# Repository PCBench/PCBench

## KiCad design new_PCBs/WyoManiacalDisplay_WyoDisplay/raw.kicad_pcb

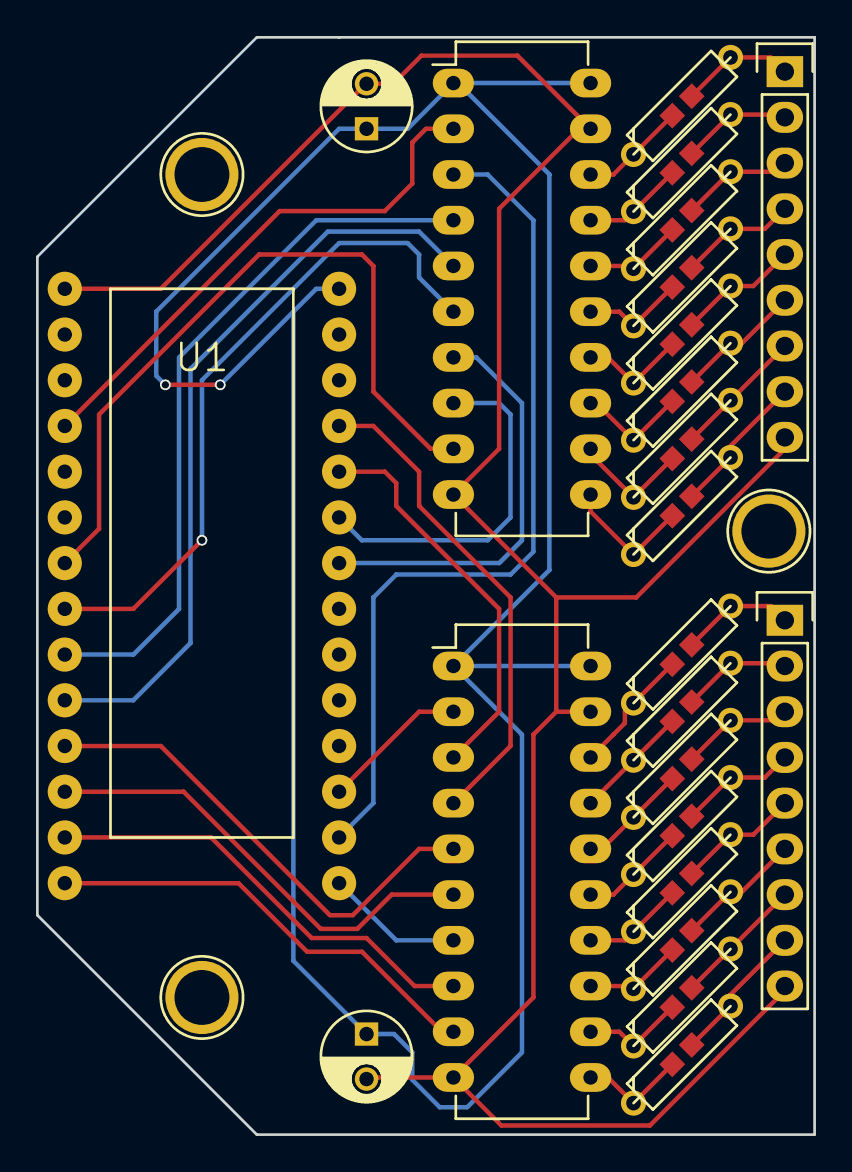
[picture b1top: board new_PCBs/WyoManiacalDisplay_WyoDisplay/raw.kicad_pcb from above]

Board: 2 copper layers, 43.2 x 61.0 mm, 23 parts (0 on the bottom side), 50 nets.

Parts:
C1, C2: 0.1uF; C_Radial_D5_L6_P2.5
P1: OUT1; Socket_Strip_Straight_1x09
P2: OUT2; Socket_Strip_Straight_1x09
R1, R2, R3, R4, R5, R6, R7, R8, R9, R10, R11, R12, R13, R14, R15, R16: R_Small; R-1-8w
U1: Teensy_3.1; Teensy-3.1
U2, U3: 74HCT245; DIP-20_W7.62mm_LongPads

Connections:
2: U1.2, U2.2
5: U1.5, U2.9
6: U1.6, U2.6
7: U1.7, U2.4
8: U1.8, U2.5
9: U1.9, U3.5
10: U1.10, U3.6
11: U1.11, U3.8
12: U1.12, U3.9
13: U1.13, U3.7
14: U1.14, U2.3
15: U1.15, U3.2
20: U1.20, U2.7
21: U1.21, U2.8
22: U1.22, U3.3
23: U1.23, U3.4
GND: C1.2, C2.2, P1.9, P2.9, U1.27, U2.10, U2.19, U3.10, U3.19
unnamed: P1.1, R1.2
unnamed: P1.2, R2.2
unnamed: P1.3, R3.2
unnamed: P1.4, R4.2
unnamed: P1.5, R5.2
unnamed: P1.6, R6.2
unnamed: P1.7, R7.2
unnamed: P1.8, R8.2
unnamed: P2.1, R9.2
unnamed: P2.2, R10.2
unnamed: P2.3, R11.2
unnamed: P2.4, R12.2
unnamed: P2.5, R13.2
unnamed: P2.6, R14.2
unnamed: P2.7, R15.2
unnamed: P2.8, R16.2
unnamed: R1.1, U2.18
unnamed: R2.1, U2.17
unnamed: R3.1, U2.16
unnamed: R4.1, U2.15
unnamed: R5.1, U2.14
unnamed: R6.1, U2.13
unnamed: R7.1, U2.12
unnamed: R8.1, U2.11
unnamed: R9.1, U3.18
unnamed: R10.1, U3.17
unnamed: R11.1, U3.16
unnamed: R12.1, U3.15
unnamed: R13.1, U3.14
unnamed: R14.1, U3.13
unnamed: R15.1, U3.12
unnamed: R16.1, U3.11
VCC: C1.1, C2.1, U1.26, U2.1, U2.20, U3.1, U3.20

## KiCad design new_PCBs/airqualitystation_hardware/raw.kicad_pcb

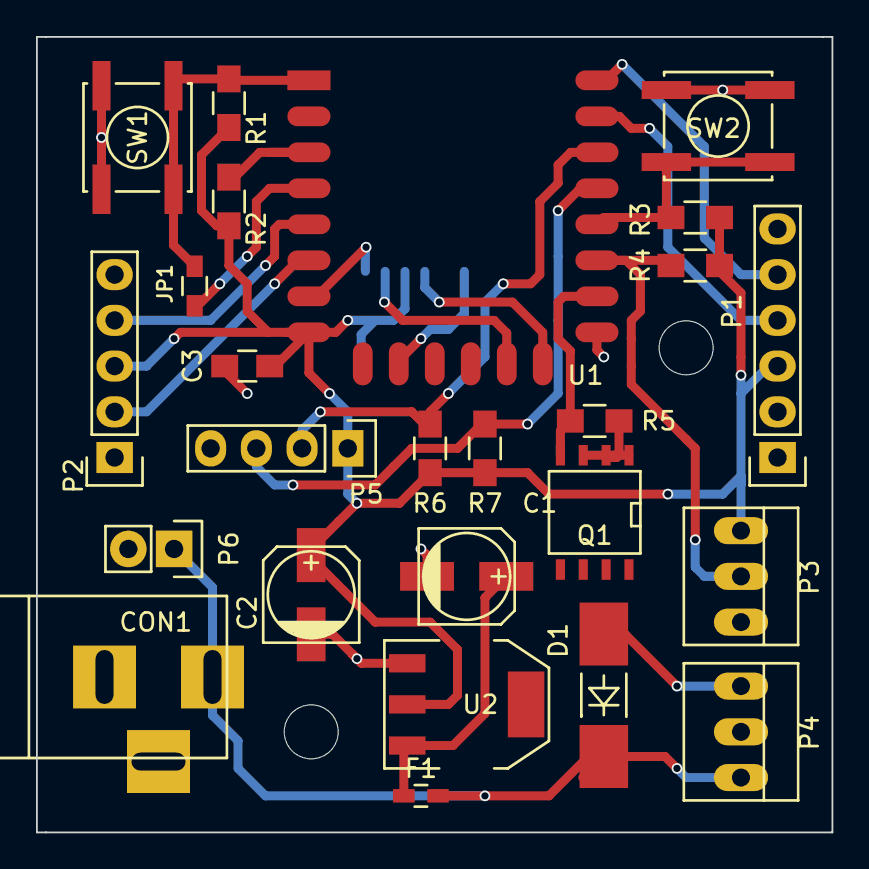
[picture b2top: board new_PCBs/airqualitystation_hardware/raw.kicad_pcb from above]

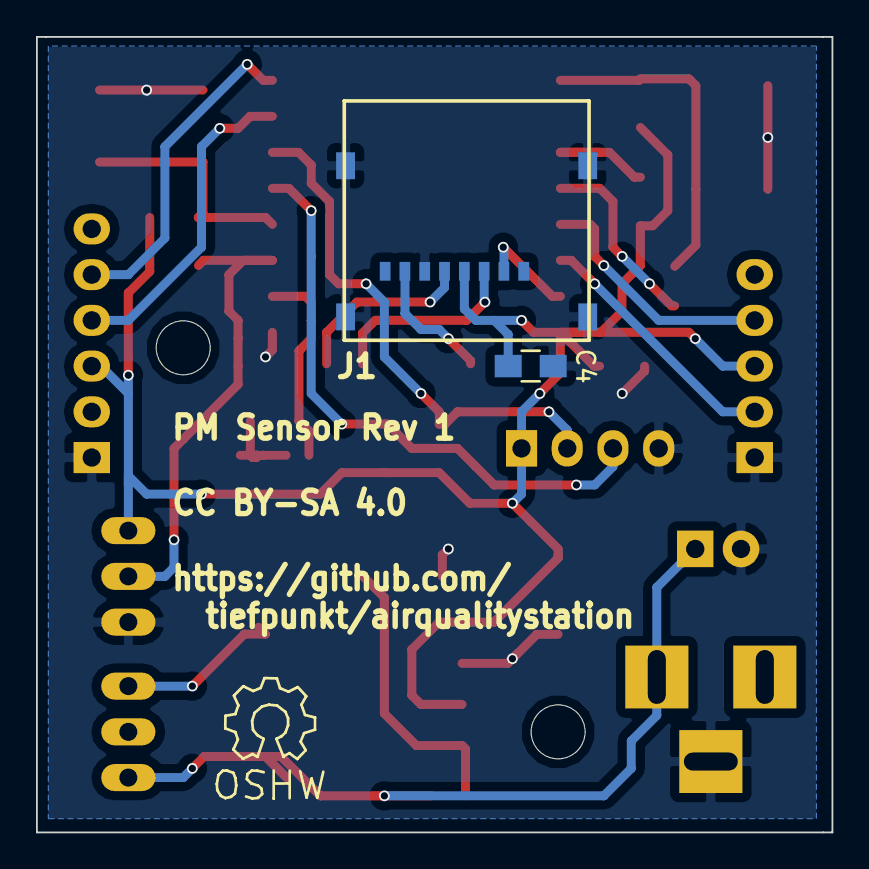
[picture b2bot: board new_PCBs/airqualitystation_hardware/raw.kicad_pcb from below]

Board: 2 copper layers, 44.2 x 44.2 mm, 27 parts (2 on the bottom side), 21 nets.

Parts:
C1, C2: 10µ; c_elec_5x5.3
C3, C4: 100n; C_0805_HandSoldering
CON1: Power; BARREL_JACK
D1: D; MELF_Handsoldering
F1: 0.1A; C_0603_HandSoldering
J1: MicroSD; MICRO_SD_HINGE_AMP
JP1: Sleep; R_0603_HandSoldering
P1: FTDI ESP; Pin_Header_Straight_1x06
P2: PPD42NS; Pin_Header_Straight_1x05
P3: DHT22; PINHEAD1-3
P4: Fan; PINHEAD1-3
P5: I2C; Pin_Header_Straight_1x04
P6: 5-9V; Pin_Header_Straight_1x02
Q1: IRF7401; SOIC-8-N
R1, R2, R3, R4, R5, R6, R7: 10k; R_0805_HandSoldering
SW1: Reset; SW_SPST_EVPBF
SW2: Flash; SW_SPST_EVPBF
U1: ESP-12E
U2: TS 1117 BCW33; SOT-223

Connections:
+9V: CON1.1, D1.1, F1.1, P4.3, P6.1
GND: C1.2, C2.2, C3.2, C4.2, CON1.3, J1.6, J1.SHLD, P1.1, P2.1, P3.3, P5.4, P6.2, Q1.1, Q1.2, Q1.3, R5.2, SW1.2, SW2.2, U1.15, U2.1
unnamed: C1.1, F1.2, U2.3
unnamed: D1.2, P4.1, Q1.5, Q1.6, Q1.7
unnamed: J1.2, U1.7
unnamed: J1.3, U1.13
unnamed: J1.5, U1.14
unnamed: J1.7, U1.10
unnamed: JP1.1, U1.4
unnamed: JP1.2, R1.2, SW1.1, U1.1
unnamed: P1.4, U1.21
unnamed: P1.5, U1.22
unnamed: P2.2, U1.6
unnamed: P2.4, U1.5
unnamed: P3.2, R4.2, U1.17
unnamed: P5.2, R6.2, U1.20
unnamed: P5.3, R7.2, U1.19
unnamed: Q1.4, R5.1, U1.16
unnamed: R2.2, U1.3
unnamed: R3.2, SW2.1, U1.18
VCC: C2.1, C3.1, C4.1, J1.4, P1.3, P2.3, P3.1, P5.1, R1.1, R2.1, R3.1, R4.1, R6.1, R7.1, U1.8, U2.2

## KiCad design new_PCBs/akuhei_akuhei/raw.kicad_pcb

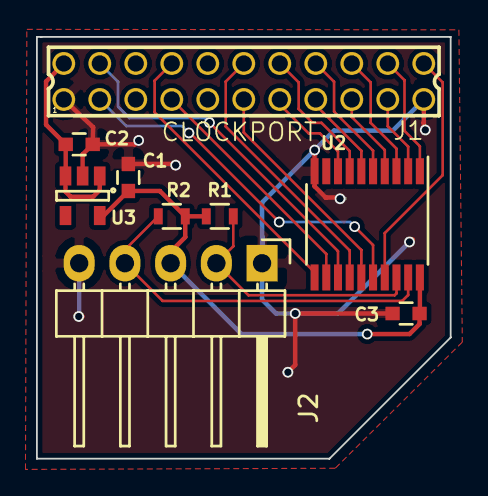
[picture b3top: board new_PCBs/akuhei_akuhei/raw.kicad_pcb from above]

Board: 2 copper layers, 23.0 x 23.4 mm, 9 parts (0 on the bottom side), 20 nets.

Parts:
C1: 1uF; C_0603
C2: 0.1uF; C_0603
C3: 100nF; C_0603
J1: CLOCKPORT; 87758-2216
J2: I2C; Pin_Header_Angled_1x05
R1, R2: 4.7k; R_0603
U2: PCA9564; TSSOP-20_4.4x6.5mm_Pitch0.65mm
U3: TLV70233DBV; SOT-23-5

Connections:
+3V3: C1.1, C3.1, J2.3, R1.2, R2.2, U2.20, U3.5
+5V: C2.1, J1.2, U3.1, U3.3
/A1: J1.12, U2.14
/A2: J1.11, U2.15
/D0: J1.20, U2.1
/D1: J1.19, U2.2
/D2: J1.18, U2.3
/D3: J1.17, U2.4
/D4: J1.16, U2.5
/D5: J1.15, U2.6
/D6: J1.14, U2.7
/D7: J1.13, U2.8
CP_CS: J1.4, U2.13
CP_INT: J1.3, U2.16
CP_IORD: J1.7, U2.12
CP_IOWR: J1.8, U2.11
CP_RESET: J1.22, U2.17
GND: C1.2, C2.2, C3.2, J1.1, J1.21, J2.1, J2.5, U2.10, U3.2
SCL: J2.2, R1.1, U2.18
SDA: J2.4, R2.1, U2.19

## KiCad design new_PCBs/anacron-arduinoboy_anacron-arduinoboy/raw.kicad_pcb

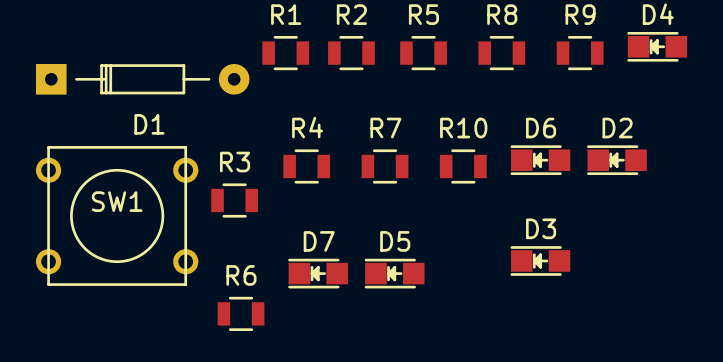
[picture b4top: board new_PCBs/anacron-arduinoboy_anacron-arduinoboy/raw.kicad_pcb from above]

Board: 2 copper layers, 18 parts (0 on the bottom side), 9 nets, no tracks yet.

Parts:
D1: D; Diode_DO-35_SOD27_Horizontal_RM10
D2, D3, D4, D5, D6, D7: LED; LED-0805
R1, R2: 220; R_0805
R3: 270; R_0805
R4, R5, R6, R7, R8, R9, R10: 2000; R_0805
SW1: SW_PUSH; SW_PUSH_SMALL

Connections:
GND: D2.1, D3.1, D4.1, D5.1, D6.1, D7.1, R4.2
unnamed: D1.1, R2.2
unnamed: D2.2, R5.1
unnamed: D3.2, R6.1
unnamed: D4.2, R7.1
unnamed: D5.2, R8.2
unnamed: D6.2, R9.1
unnamed: D7.2, R10.1
unnamed: R4.1, SW1.2

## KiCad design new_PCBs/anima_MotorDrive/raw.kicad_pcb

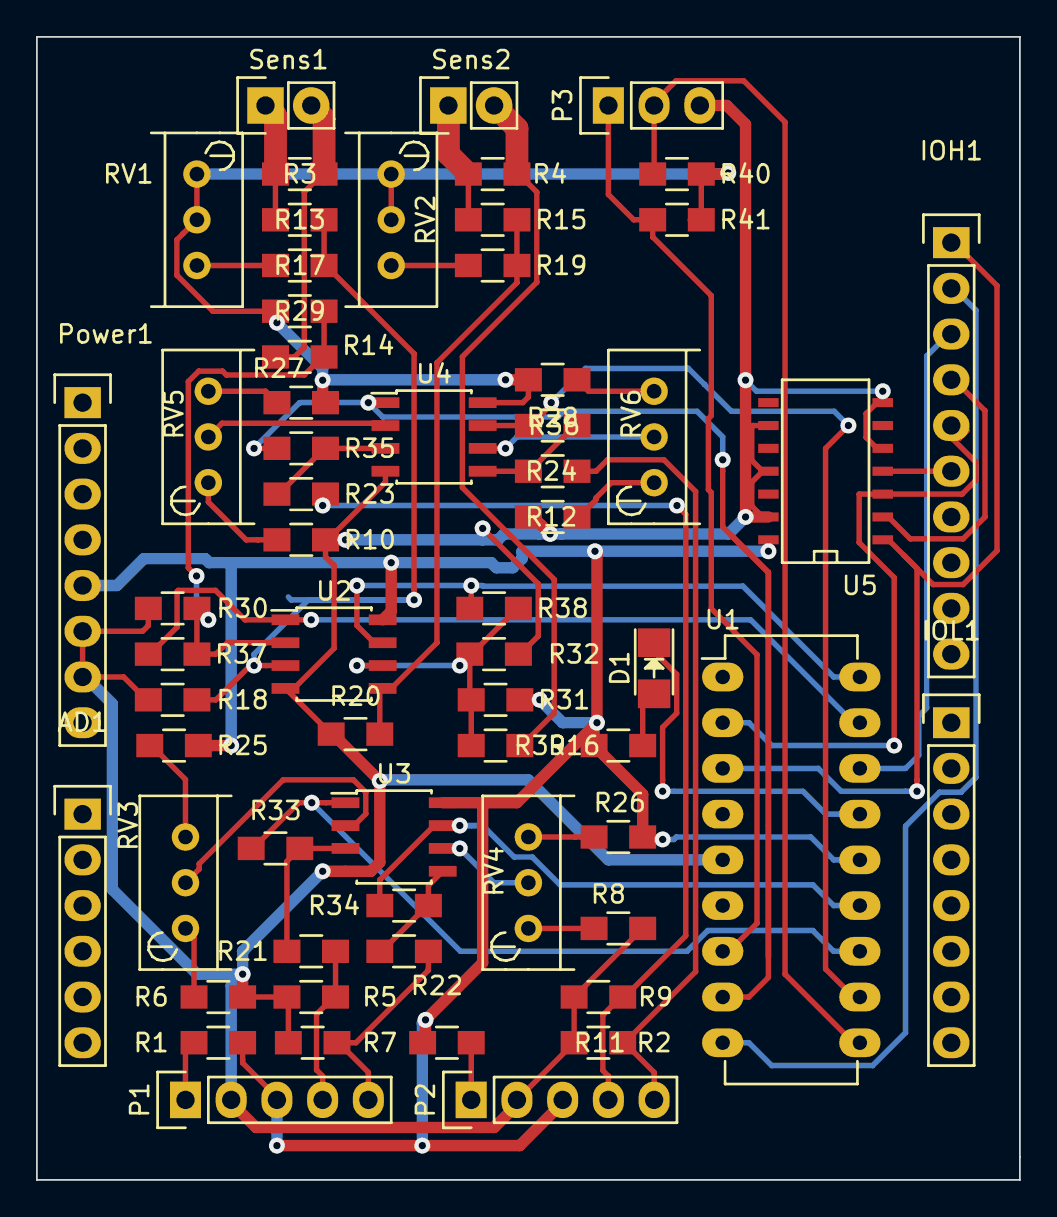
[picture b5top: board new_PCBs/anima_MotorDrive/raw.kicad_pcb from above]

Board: 2 copper layers, 54.6 x 63.5 mm, 62 parts (0 on the bottom side), 50 nets.

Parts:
AD1: CONN_01X06; Pin_Header_Straight_1x06
D1: LED; LED-1206
IOH1: CONN_01X10; Pin_Header_Straight_1x10
IOL1: CONN_01X08; Pin_Header_Straight_1x08
P1, P2: CONN_01X05; Pin_Header_Straight_1x05
P3: CONN_01X03; Pin_Header_Straight_1x03
Power1: CONN_01X08; Pin_Header_Straight_1x08
R1, R2, R3, R4, R5, R6, R7, R8, R9, R10, R11, R12, R13, R14, R15, R16, R17, R18, R19, R20, R21, R22, R23, R24, R25, R26, R27, R28, R29, R30, R31, R32, R33, R34, R35, R36, R37, R38, R39, R40, R41: R; R_0805_HandSoldering
RV1, RV2, RV3, RV4, RV5, RV6: POT; Potentiometer_Bourns_3296W_3-8Zoll_Inline_ScrewUp
Sens1, Sens2: CONN_01X02; Pin_Header_Straight_1x02
U1: PIC16(L)F1847-I/P; DIP-18_W7.62mm_LongPads
U2, U3, U4: LM358N; SOIC-8_3.9x4.9mm_Pitch1.27mm
U5: 74HC04; SOIC-14_N

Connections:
+5V: P1.3, P2.3, Power1.5, R1.1, R2.1, R25.2, R26.2, R27.2, R28.2, R29.2, R31.2, R39.1, R40.1, R41.1, RV1.1, RV1.2, RV2.1, RV2.2, U1.14, U2.8, U3.8, U4.8, U5.14
GND: P1.2, P2.2, P3.3, Power1.6, Power1.7, R5.1, R6.2, R7.1, R8.2, R9.1, R10.2, R11.1, R12.2, R18.1, R20.1, R30.1, R32.1, U1.5, U2.4, U3.4, U4.4, U5.5, U5.7, U5.9, U5.11, U5.13
unnamed: D1.1, U1.15
unnamed: D1.2, R39.2
unnamed: IOH1.1, U1.3, U5.1
unnamed: IOH1.2, U1.9
unnamed: IOH1.3, U1.16
unnamed: IOH1.4, U5.2
unnamed: IOH1.5, U1.2, U5.3
unnamed: IOH1.6, U5.4
unnamed: P1.1, R1.2
unnamed: P1.4, R5.2, R21.2
unnamed: P1.5, R7.2, R22.2
unnamed: P2.1, R2.2
unnamed: P2.4, R9.2, R23.2
unnamed: P2.5, R11.2, R24.2
unnamed: P3.1, R41.2, U1.7
unnamed: P3.2, R40.2, U1.10
unnamed: R6.1, RV3.1
unnamed: R8.1, RV4.1
unnamed: R10.1, RV5.1
unnamed: R12.1, RV6.1
unnamed: R13.1, R17.1, R18.2, U2.3
unnamed: R3.2, R13.2, Sens1.1
unnamed: R14.1, R29.1, R30.2, R37.2, U2.2
unnamed: R3.1, R14.2, Sens1.2
unnamed: R15.1, R19.1, R20.2, U2.5
unnamed: R4.2, R15.2, Sens2.1
unnamed: R16.1, R31.1, R32.2, R38.2, U2.6
unnamed: R4.1, R16.2, Sens2.2
unnamed: R17.2, RV1.3
unnamed: R19.2, RV2.3
unnamed: R21.1, R33.2, U3.3
unnamed: R22.1, R34.2, U3.5
unnamed: R23.1, R35.2, U4.3
unnamed: R24.1, R36.2, U4.5
unnamed: R25.1, RV3.3
unnamed: R26.1, RV4.3
unnamed: R27.1, RV5.3
unnamed: R28.1, RV6.3
unnamed: R33.1, U1.12, U3.1
unnamed: R34.1, U1.13, U3.7
unnamed: R35.1, U1.8, U4.1
unnamed: R36.1, U1.11, U4.7
unnamed: R37.1, U1.17, U2.1
unnamed: R38.1, U1.18, U2.7
unnamed: RV3.2, U3.2
unnamed: RV4.2, U3.6
unnamed: RV5.2, U4.2
unnamed: RV6.2, U4.6

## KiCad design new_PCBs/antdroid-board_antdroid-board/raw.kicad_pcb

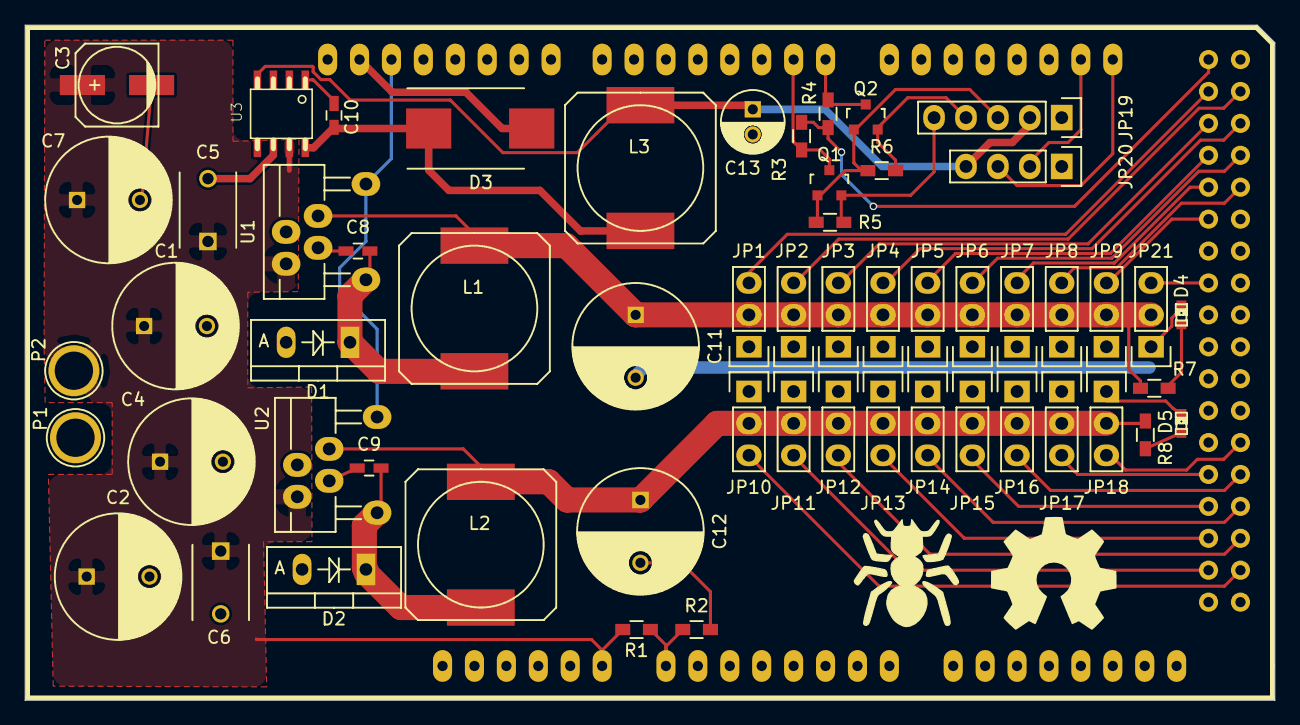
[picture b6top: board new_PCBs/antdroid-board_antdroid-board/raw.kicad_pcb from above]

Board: 2 copper layers, 99.4 x 53.7 mm, 58 parts (0 on the bottom side), 42 nets.

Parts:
C1, C2, C3, C4: 470µF/25V; C_Radial_D10_L13_P5
C5, C6: 0.47µF; C_Disc_D6_P5
C7: 100µF/25V; c_elec_6.3x7.7
C8, C9, C10: 10nF; C_0603_HandSoldering
C11, C12: 1000µF/16V; C_Radial_D10_L16_P5
C13: 100µF/16V; C_Radial_D5_L11_P2
D1, D2: MBR745G; Diode_TO-220_Vertical
D3: MBRS340; Diode-DO-214AB_Handsoldering
D4, D5: LED; LED-0603
JP1, JP2, JP3, JP4, JP5, JP6, JP7, JP8, JP9, JP10, JP11, JP12, JP13, JP14, JP15, JP16, JP17, JP18, JP21: PINHD-1X3_2.54; Pin_Header_Straight_1x03
JP19: PINHD-1X5; Pin_Header_Straight_1x05
JP20: PINHD-1X4_2.54; Pin_Header_Straight_1x04
L1, L2: 15µH/5.8A; SELF-WE-PD-XXL
L3: 47µH/2A; SELF-WE-PD-XXL
P1, P2: CONN_01X01; 1pin
Q1, Q2: BSS138; SOT-23
R1: 33K; R_0603_HandSoldering
R2, R3, R4, R5, R6: 10K; R_0603_HandSoldering
R7, R8: 1KΩ; R_0603_HandSoldering
SHIELD1: ARDUINO_MEGA_SHIELD; ArduinoMegaShield
U1, U2: LM2678T-5.0; TO-220-7C
U3: LM2675M-5; AB2_SO08

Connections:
+3V3: JP19.3, Q1.1, Q2.1, R5.1, R6.1
+5V: C13.1, JP19.2, JP20.4, L3.1, U3.4
+5VA: C11.1, JP1.2, JP2.2, JP3.2, JP4.2, JP5.2, JP6.2, JP7.2, JP8.2, JP9.2, JP21.2, L1.1, R7.1, U1.6
+5VD: C12.1, JP10.2, JP11.2, JP12.2, JP13.2, JP14.2, JP15.2, JP16.2, JP17.2, JP18.2, L2.1, R8.1, U2.6
+5VP: R3.1, R4.1, SHIELD1.5V_4
/AUX: JP21.3, SHIELD1.34
/LFC: JP1.3, SHIELD1.22
/LFF: JP2.3, SHIELD1.23
/LFT: JP3.3, SHIELD1.24
/LMC: JP4.3, SHIELD1.25
/LMF: JP5.3, SHIELD1.26
/LMT: JP6.3, SHIELD1.27
/LRC: JP7.3, SHIELD1.28
/LRF: JP8.3, SHIELD1.29
/LRT: JP9.3, SHIELD1.30
/RFC: JP10.3, SHIELD1.53
/RFF: JP11.3, SHIELD1.52
/RFT: JP12.3, SHIELD1.51
/RMC: JP13.3, SHIELD1.50
/RMF: JP14.3, SHIELD1.49
/RMT: JP15.3, SHIELD1.48
/RPI_RX: JP19.5, Q1.2, R5.2
/RPI_TX: JP19.4, Q2.2, R6.2
/RRC: JP16.3, SHIELD1.47
/RRF: JP17.3, SHIELD1.46
/RRT: JP18.3, SHIELD1.45
/RX0: Q2.3, R4.2, SHIELD1.0
/SERVO_ON: SHIELD1.13, U1.7, U2.7
/TX0: Q1.3, R3.2, SHIELD1.1
GND: C1.2, C2.2, C3.2, C4.2, C5.2, C6.2, C7.2, C11.2, C12.2, C13.2, D1.2, D2.2, D3.2, D4.1, D5.1, JP1.1, JP2.1, JP3.1, JP4.1, JP5.1, JP6.1, JP7.1, JP8.1, JP9.1, JP10.1, JP11.1, JP12.1, JP13.1, JP14.1, JP15.1, JP16.1, JP17.1, JP18.1, JP19.1, JP20.1, JP21.1, P1.1, R2.2, SHIELD1.GND1, SHIELD1.GND2, SHIELD1.GND3, SHIELD1.GND4, SHIELD1.GND5, U1.4, U2.4, U3.6
unnamed: C8.1, U1.3
unnamed: C8.2, D1.1, L1.2, U1.1
unnamed: C9.1, U2.3
unnamed: C9.2, D2.1, L2.2, U2.1
unnamed: C10.1, D3.1, L3.2, U3.8
unnamed: C10.2, U3.1
unnamed: D4.2, R7.2
unnamed: D5.2, R8.2
unnamed: JP20.2, SHIELD1.20
unnamed: JP20.3, SHIELD1.21
unnamed: R1.2, R2.1, SHIELD1.AD0
VCC: C1.1, C2.1, C3.1, C4.1, C5.1, C6.1, C7.1, P2.1, R1.1, SHIELD1.V_IN, U1.2, U2.2, U3.7

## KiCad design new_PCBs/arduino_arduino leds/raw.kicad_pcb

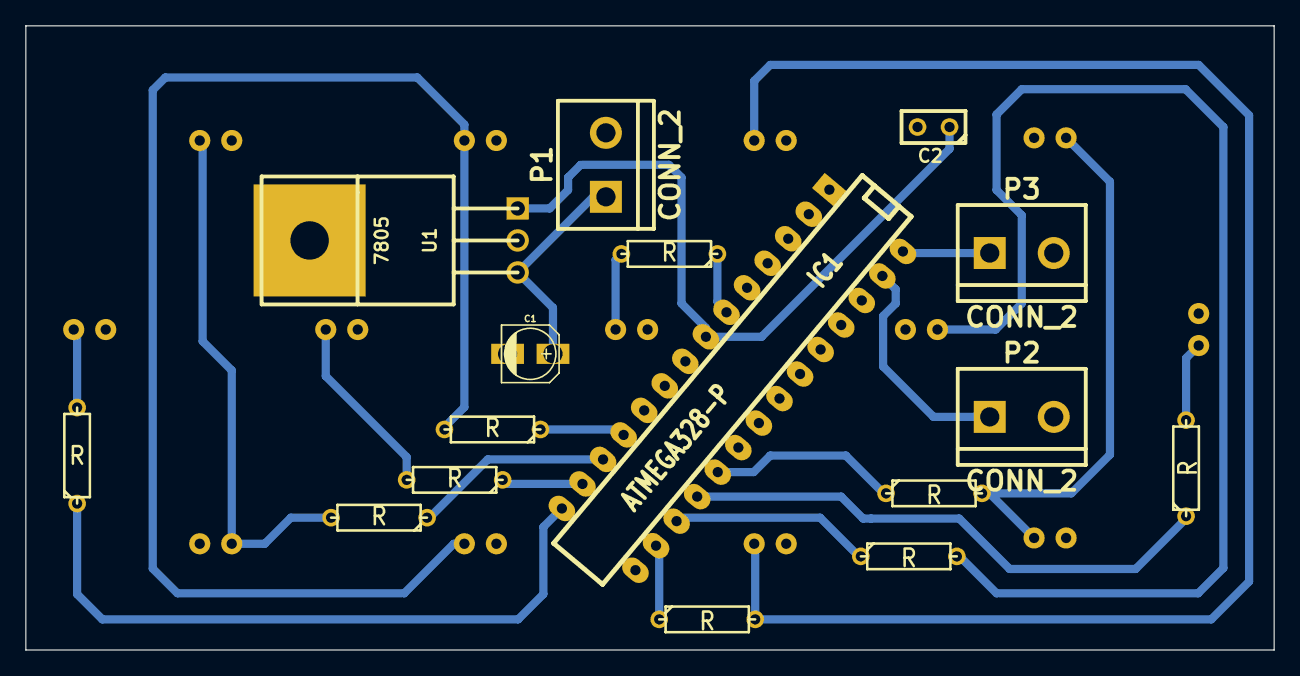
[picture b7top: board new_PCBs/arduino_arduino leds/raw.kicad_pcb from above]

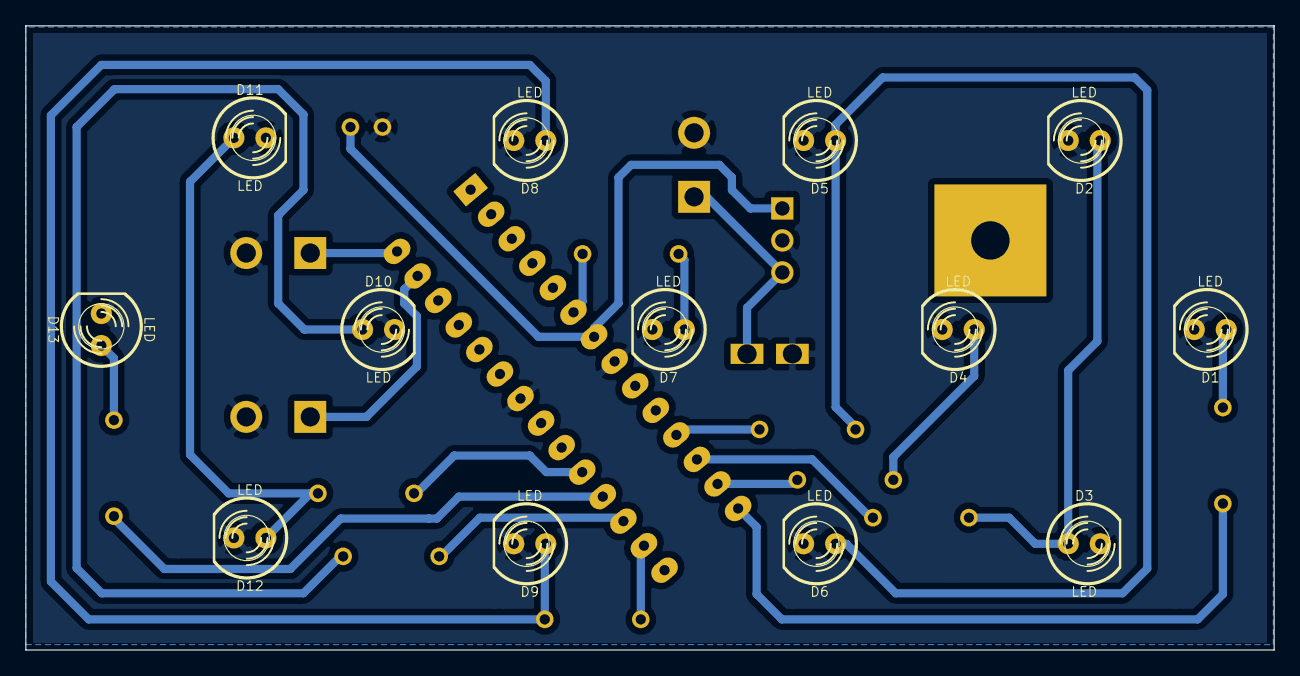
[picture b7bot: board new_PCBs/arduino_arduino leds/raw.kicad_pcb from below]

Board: 2 copper layers, 99.1 x 49.5 mm, 29 parts (13 on the bottom side), 23 nets.

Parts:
C1: CAPAPOL; c_elec_4x5.8
C2: C; C1
D1, D2, D3, D4, D5, D6, D7, D8, D9, D10, D11, D12, D13: LED; LED-5MM
IC1: ATMEGA328-P; DIP-28__300_ELL
P1, P2, P3: CONN_2; bornier2
R1, R2, R3, R4, R5, R6, R7, R8, R9: R; R3
U1: 7805; TO220

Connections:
/BTN1: IC1.27, P2.1
/BTN2: IC1.28, P3.1
/PIN4: IC1.6, R5.1
/PIN5: IC1.11, R4.1
/PIN6: IC1.12, R2.1
/PIN7: IC1.13, R3.1
/PIN8: IC1.14, R1.1
/PIN10: IC1.16, R6.1
/PIN11: IC1.17, R7.1
/PIN12: IC1.18, R9.1
/PIN13: IC1.19, R8.1
/VI: C1.1, P1.1, U1.2
/VO: C2.1, IC1.7, U1.1
GND: C1.2, C2.2, D1.2, D2.2, D3.2, D4.2, D5.2, D6.2, D7.2, D8.2, D9.2, D10.2, D11.2, D12.2, D13.2, IC1.8, IC1.22, P1.2, P2.2, P3.2, U1.3
unnamed: D7.1, R5.2
unnamed: D10.1, R7.2
unnamed: D13.1, R9.2
unnamed: D1.1, R1.2
unnamed: D4.1, R3.2
unnamed: D2.1, D3.1, R2.2
unnamed: D8.1, D9.1, R6.2
unnamed: D11.1, D12.1, R8.2
unnamed: D5.1, D6.1, R4.2

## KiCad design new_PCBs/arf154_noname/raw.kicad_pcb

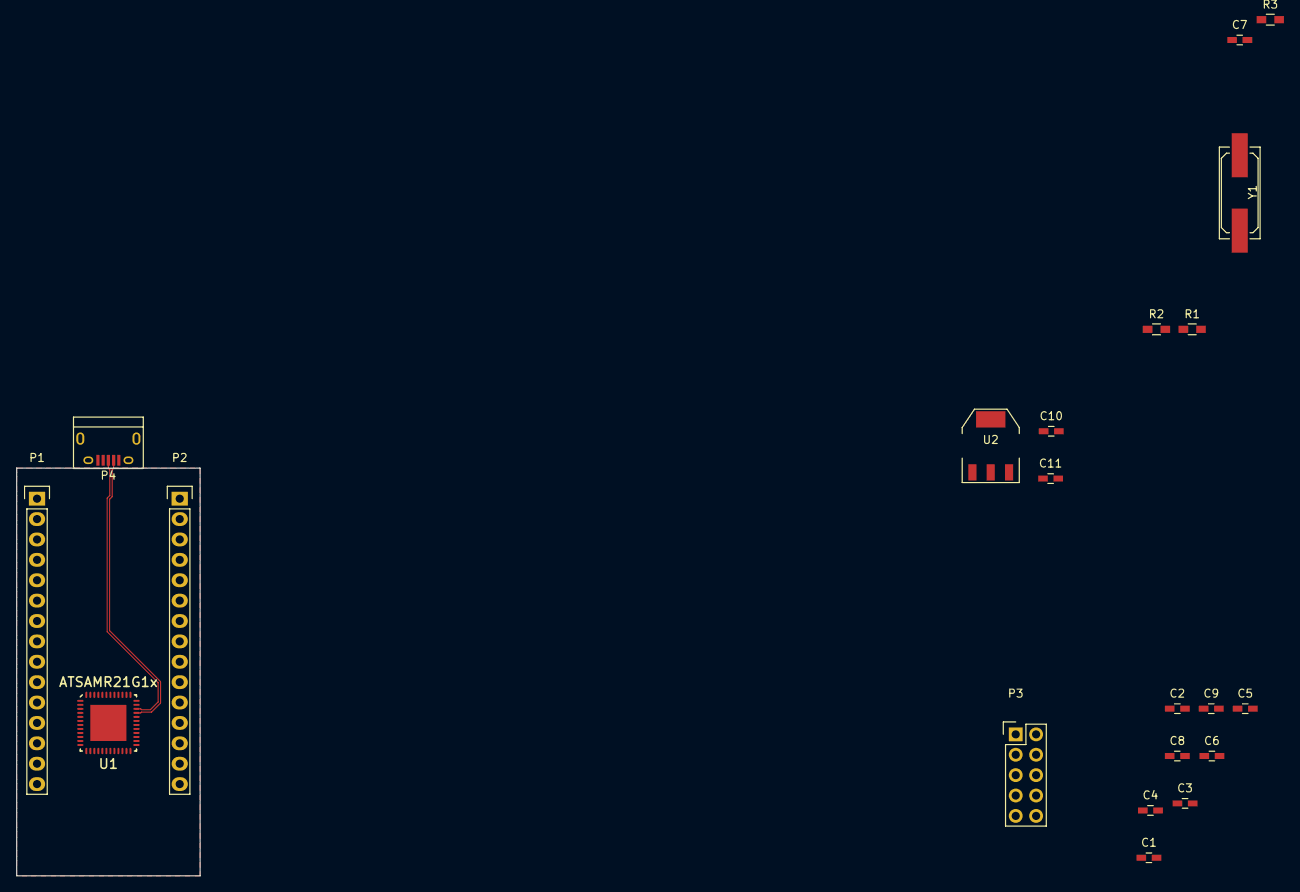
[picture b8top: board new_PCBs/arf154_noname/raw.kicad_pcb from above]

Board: 4 copper layers, 22.9 x 50.8 mm, 21 parts (0 on the bottom side), 14 nets.

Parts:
C1: 10uF; C_0603_HandSoldering
C2, C3, C4, C5, C6, C7, C8, C10: 100n; C_0603_HandSoldering
C9, C11: 10u; C_0603_HandSoldering
P1, P2: CONN_01X15; Pin_Header_Straight_1x15
P3: CONN_02X05; Pin_Header_Straight_2x05
P4: USB_B; USB_Micro-B
R1, R2: 100K; R_0603_HandSoldering
R3: 10K; R_0603_HandSoldering
U1: ATSAMR21G1x; QFN48EP
U2: LD1117S33TR; SOT-223
Y1: 16MHz; Q_49U3HMS

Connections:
/MainProcessor/PA22: U1.31, U1.37
/MainProcessor/PA23: R1.2, R2.1, U1.32, U1.38
/MainProcessor/RST: C7.1, P3.10, R3.2, U1.40
/MainProcessor/SWCLK: P3.4, U1.45
/MainProcessor/SWDIO: P3.2, U1.46
/Sheet557215E3/D+: P4.2, U1.33
/Sheet557215E3/D-: P4.3, U1.34
GND: C1.2, C2.2, C3.2, C4.2, C5.2, C7.2, C10.2, C11.2, P3.3, P3.5, P3.9, P4.4, P4.5, R2.2, U1.14, U1.29, U1.35, U1.42, U2.1
GNDA: C6.2, C8.2, C9.2, U1.5, U1.8, U1.17, U1.20
unnamed: U1.3, Y1.1
unnamed: U1.4, Y1.2
VAA: C6.1, C8.1, C9.1, U1.6, U1.7
VCC: C10.1, P4.1, R1.1, U2.3
VDD: C1.1, C2.1, C3.1, C4.1, C5.1, C11.1, P3.1, R3.1, U1.13, U1.30, U1.36, U1.43, U1.44, U2.2

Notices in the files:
new_PCBs/airqualitystation_hardware/raw.kicad_pcb:
CC BY-SA 4.0
